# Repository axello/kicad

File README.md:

# kicad playground

Just starting with kicad, this is a hodgepodge of small electronics projects, mostly centered around the ESP8266.

## ESP-RS232
A small-footprint design to connect an ESP8266 to a DB9 RS232 interface. Useful to connect to powerbars, power supplies, air quality sensors, solar panel controllers and whatnot.

## ESP-Sensors
A design to test the non-breadboardable ESP8266-12E with various sensors. It has a small prototyping area to solder different sensors on.

## GettingToBlinky
First kicad tutorial by [Contextual Electronics](https://www.youtube.com/watch?v=JN_Y93RTdSo&list=PLy2022BX6Eso532xqrUxDT1u2p4VVsg-q>)

## NodeMCU-Metriful
I wanted to hook up the Kickstarted [Metriful](https://www.kickstarter.com/projects/metriful/sense-indoor-environment-monitor/) project to my mqtt system, so needed to hook it up to the wifi. I decided to use the plethora of NodeMCUs I had laying around and made this dedicated circuit board for it. As a bonus it allows adding a chain of DS18B20 temperature sensors.
I also designed a 3D printable case for it, which you can find [here](https://cad.onshape.com/documents/7fa239791ccb4fa3d67e6539/w/d93b090168ac9bb29c0ad025/e/45795b691b4838ca7b8d4e6e).

## libs
My components

## mods
My footprints

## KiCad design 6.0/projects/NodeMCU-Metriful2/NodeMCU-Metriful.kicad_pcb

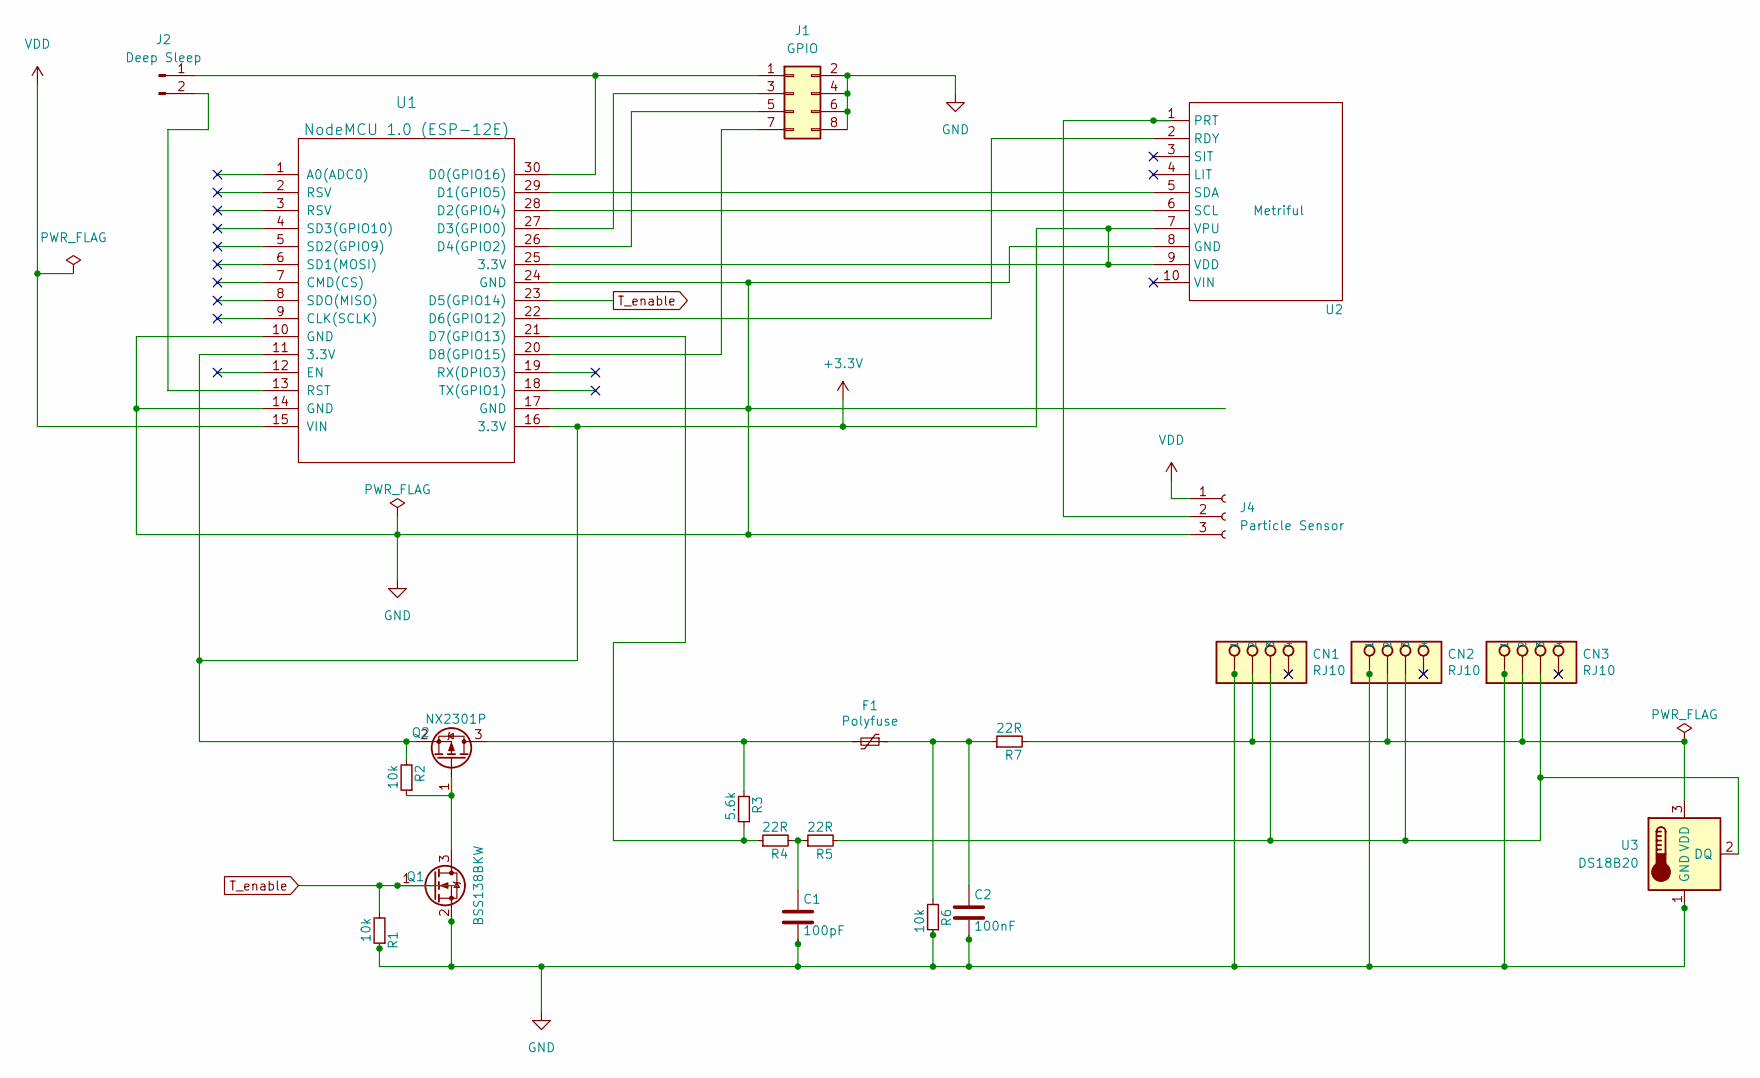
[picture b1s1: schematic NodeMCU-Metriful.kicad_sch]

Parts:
C1: 100pF; C_0805_2012Metric_Pad1.18x1.45mm_HandSolder
C2: 100nF; C_0805_2012Metric
CN1, CN2, CN3: RJ10; rj10
F1: Polyfuse; Fuse_1210_3225Metric_Pad1.42x2.65mm_HandSolder
J1: GPIO; PinHeader_2x04_P2.54mm_Vertical
J2: Deep Sleep; PinHeader_1x02_P2.54mm_Vertical
J4: Particle Sensor; JST_PH_B3B-PH-K_1x03_P2.00mm_Vertical
Q1: BSS138BKW; SOT-323_SC-70_Handsoldering
Q2: NX2301P; SOT-23-3
R1, R2, R6: 10k; R_0805_2012Metric_Pad1.20x1.40mm_HandSolder
R3: 5.6k; R_0805_2012Metric_Pad1.20x1.40mm_HandSolder
R4, R5, R7: 22R; R_0805_2012Metric_Pad1.20x1.40mm_HandSolder
U1: NodeMCU 1.0 (ESP-12E); NodeMCU_0.1_Axel
U2: Metriful; Metriful-1
U3: DS18B20; TO-92_Inline

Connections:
+3V3: Q2.2 (S), R2.2, U1.11 (3.3V), U1.16 (3.3V), U1.25 (3.3V), U2.7 (VPU), U2.9 (VDD)
GND: C1.2, C2.2, CN1.1, CN2.1, CN3.1, J1.2, J1.4, J1.6, J1.8, J4.3, Q1.2 (S), R1.1, R6.1, U1.10 (GND), U1.14 (GND), U1.17 (GND), U1.24 (GND), U2.8 (GND), U3.1 (GND)
unnamed: C1.1, R4.2, R5.1
unnamed: C2.1, F1.1, R6.2, R7.1
unnamed: CN1.2, CN2.2, CN3.2, R7.2, U3.3 (VDD)
unnamed: CN1.3, CN2.3, CN3.3, R5.2, U3.2 (DQ)
unnamed: F1.2, Q2.3 (D), R3.2
unnamed: J1.1 (D0), J2.1, U1.30 (D0(GPIO16))
unnamed: J1.3 (D3), U1.27 (D3(GPIO0))
unnamed: J1.5 (D4), U1.26 (D4(GPIO2))
unnamed: J1.7 (D8), U1.20 (D8(GPIO15))
unnamed: J2.2, U1.13 (RST)
unnamed: J4.2, U2.1 (PRT)
unnamed: Q1.3 (D), Q2.1 (G), R2.1
unnamed: R3.1, R4.1, U1.21 (D7(GPIO13))
unnamed: U1.22 (D6(GPIO12)), U2.2 (RDY)
unnamed: U1.28 (D2(GPIO4)), U2.6 (SCL)
unnamed: U1.29 (D1(GPIO5)), U2.5 (SDA)
T_enable: Q1.1 (G), R1.2, U1.23 (D5(GPIO14))
VDD: J4.1, U1.15 (VIN)

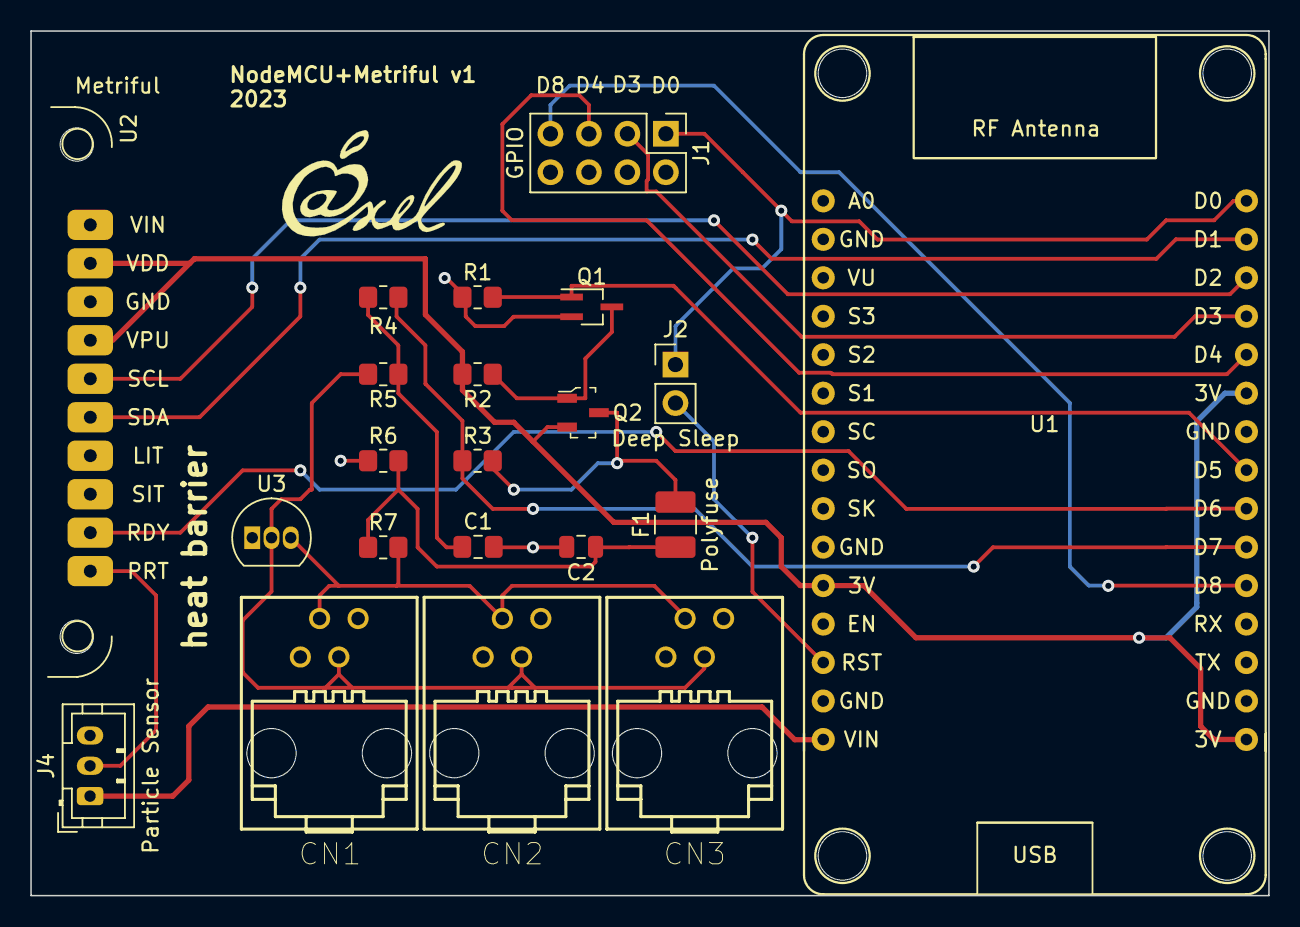
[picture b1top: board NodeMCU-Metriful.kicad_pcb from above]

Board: 2 copper layers, 81.7 x 57.1 mm, 21 parts (0 on the bottom side), 20 nets.

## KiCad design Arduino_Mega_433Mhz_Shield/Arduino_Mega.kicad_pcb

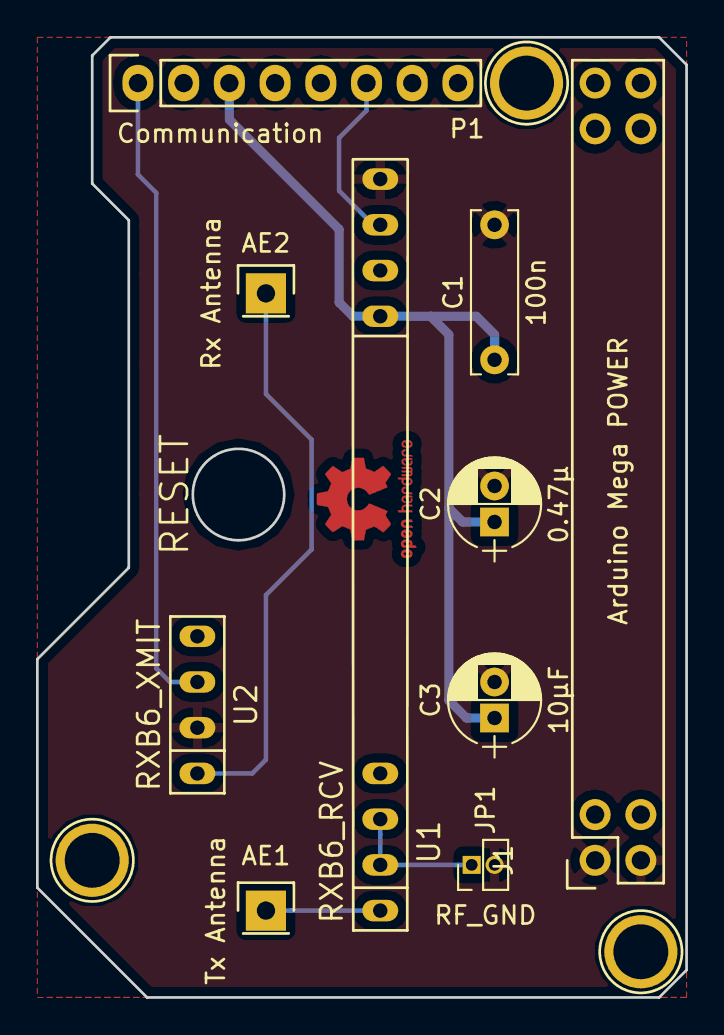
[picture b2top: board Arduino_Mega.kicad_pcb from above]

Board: 2 copper layers, 36.1 x 53.3 mm, 13 parts (0 on the bottom side), 8 nets.

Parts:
AE1: Tx Antenna; Pin_Header_Straight_1x01
AE2: Rx Antenna; Pin_Header_Straight_1x01
C1: 100n; C_Rect_L9.0mm_W2.5mm_P7.50mm_MKT
C2: 0.47µ; CP_Radial_D5.0mm_P2.00mm
C3: 10µF; CP_Radial_D5.0mm_P2.00mm
J1: Arduino Mega POWER; Power_Strip_Arduino_Mega_2x18
JP1: RF_GND; Pin_Header_Straight_1x02_Pitch1.27mm
P1: Communication; Socket_Strip_Arduino_1x08
P9, P10, P13: CONN_01X01; Arduino_1pin
U1: RXB6_RCV; RCV
U2: RXB6_XMIT; XMIT

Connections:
+5V: J1.35, J1.36, U2.4
/14(Tx3): P1.1, U2.3
/16(Tx2): C1.1, C2.1, C3.1, P1.3, U1.5
/19(Rx1): P1.6, U1.7
GND: C1.2, C2.2, C3.2, J1.1, J1.2, JP1.2, U1.8, U2.2
unnamed: AE1.1, U1.1
unnamed: AE2.1, U2.1
unnamed: JP1.1, U1.2, U1.3

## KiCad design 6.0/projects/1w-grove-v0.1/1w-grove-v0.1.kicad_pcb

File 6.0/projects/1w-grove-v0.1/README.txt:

# 1w-esp32

2021-01-30  v0.2 - version based on the rs485-esp32-v0.3 version and updated to a sub schematic
                 - Had to replace all components after moving them to the sun schema

# end

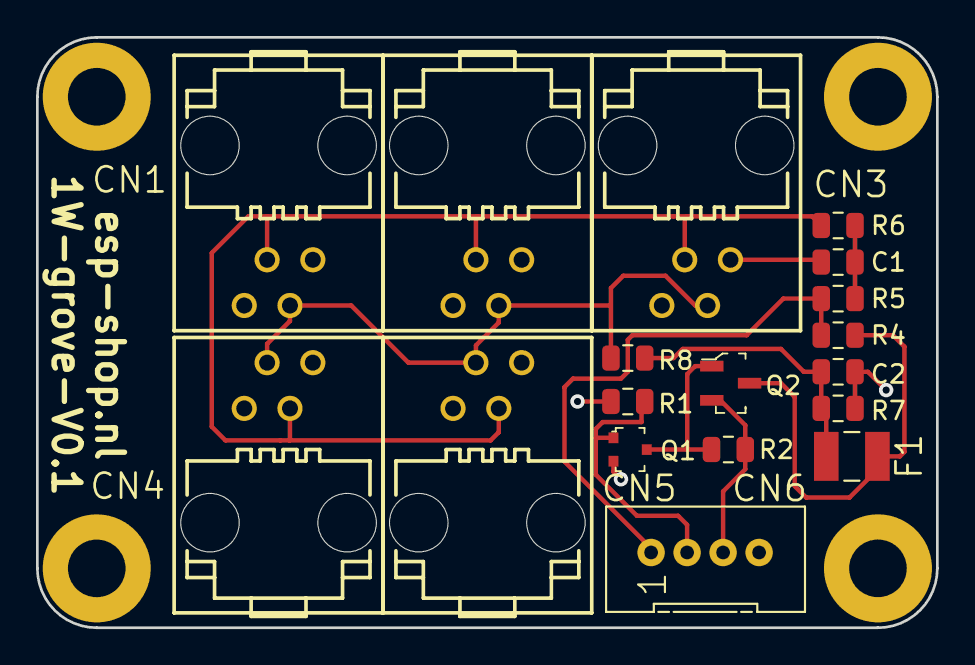
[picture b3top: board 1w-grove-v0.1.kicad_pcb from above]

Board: 2 copper layers, 50.0 x 32.8 mm, 23 parts (1 on the bottom side), 10 nets.

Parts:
C1: 100pF; C_0805_2012Metric
C2: 100nF; C_0805_2012Metric
CN1, CN2, CN3, CN4, CN5: RJ10; rj10-v2
CN6: grove; grove-v0.1
F1: Polyfuse_Small; C1210
Q1: BSS138BKW; SOT-323
Q2: NX2301P; SOT-23-3
R1, R2, R7: 10k; R_0805_2012Metric
R4: 5.6k; R_0805_2012Metric
R5, R6, R8: 22R; R_0805_2012Metric
U3: CE-mark; CE-140
U4, U6, U10, U11: schroef_3.5mm

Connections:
unnamed: C1.1, R5.2, R6.1
unnamed: C1.2, C2.2, CN1.1, CN2.1, CN3.1, CN4.1, CN5.1, CN6.4, Q1.2 (S), R1.1, R7.1
unnamed: C2.1, F1.1, R7.2, R8.1
unnamed: CN1.2, CN2.2, CN3.2, CN4.2, CN5.2, R8.2
unnamed: CN1.3, CN2.3, CN3.3, CN4.3, CN5.3, R6.2
unnamed: F1.2, Q2.3 (D), R4.2
unnamed: CN6.2, Q1.1 (G), R1.2
unnamed: Q1.3 (D), Q2.1 (G), R2.1
unnamed: CN6.3, Q2.2 (S), R2.2
unnamed: CN6.1, R4.1, R5.1

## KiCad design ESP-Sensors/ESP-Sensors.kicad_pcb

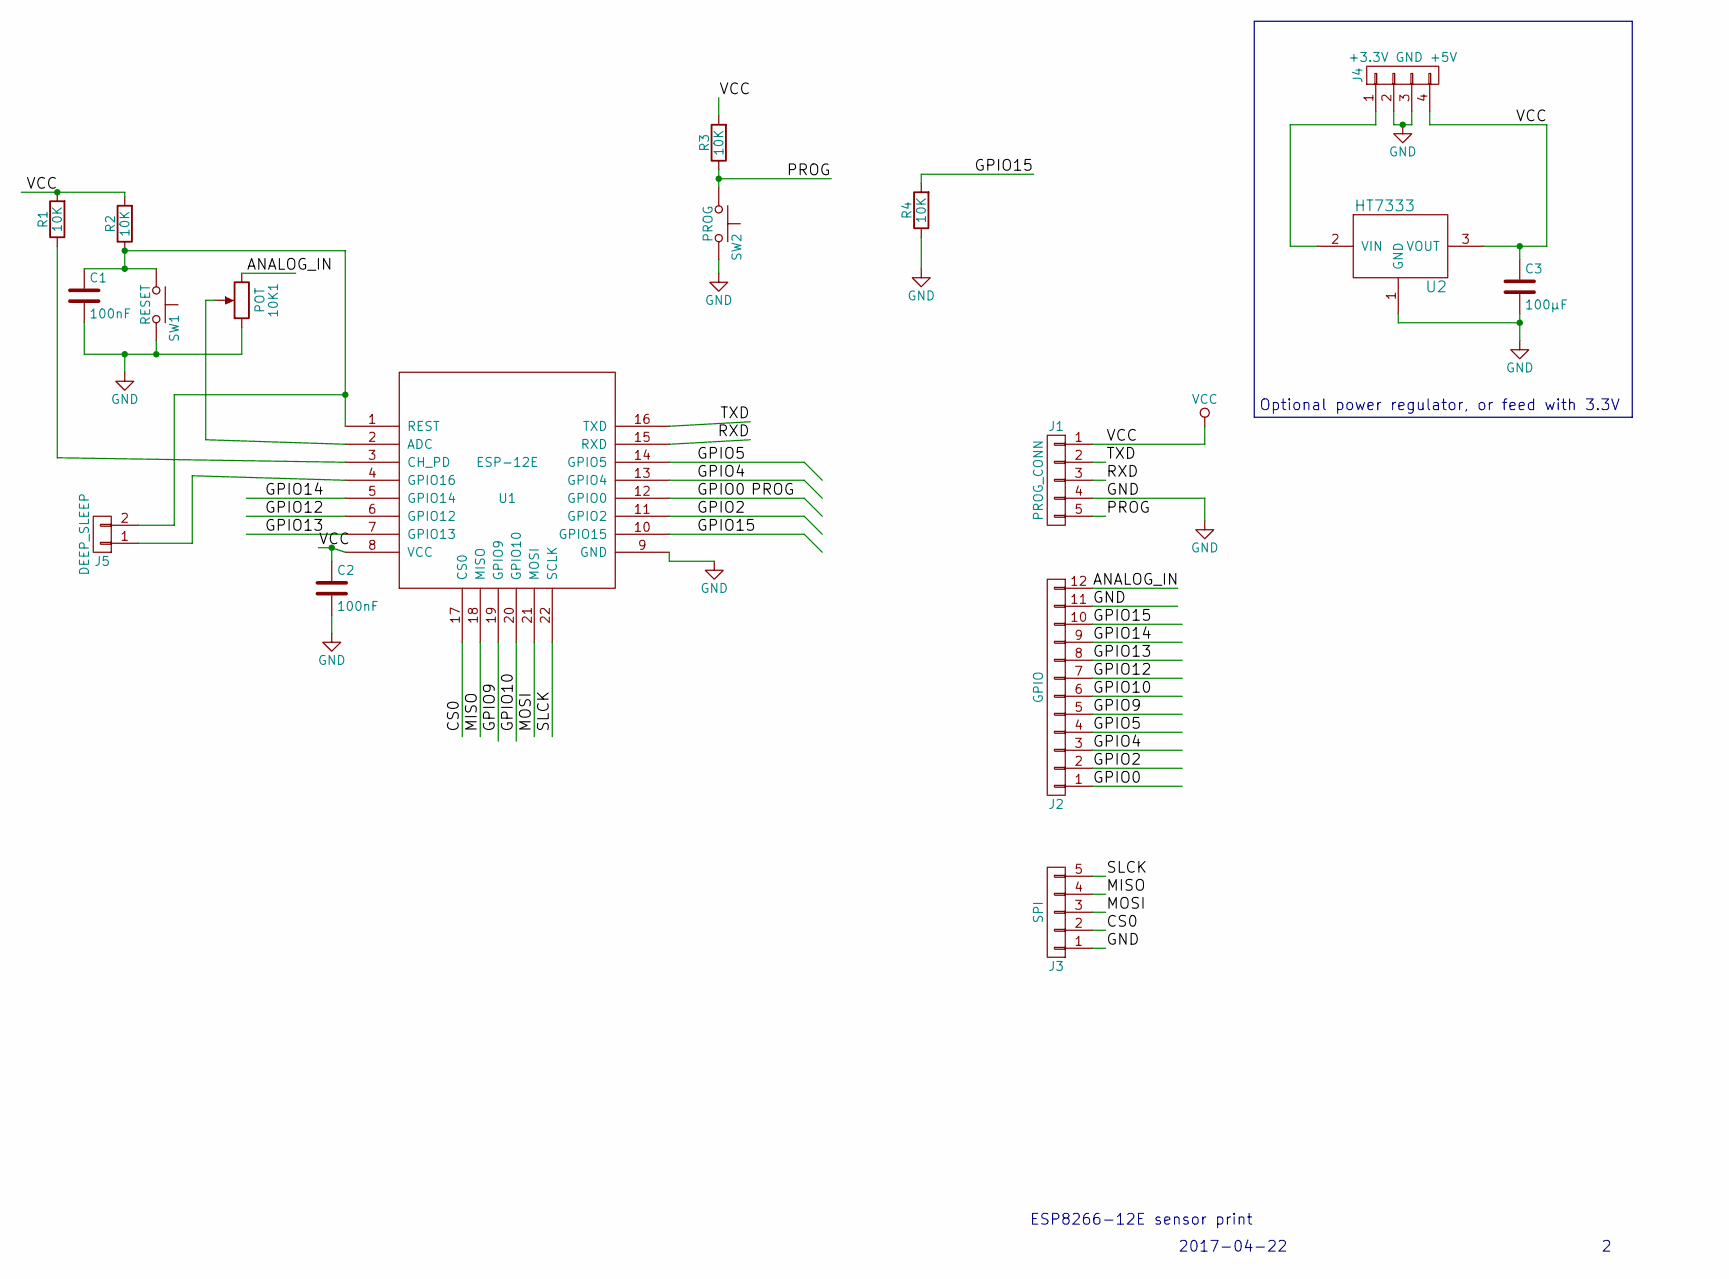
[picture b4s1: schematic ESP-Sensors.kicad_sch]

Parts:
10K1: POT; Potentiometer_Trimmer_Vishay_T73YP_Horizontal
C1, C2: 100nF; C_0805_HandSoldering
C3: 100µF; c_elec_6.3x7.7
J1: PROG_CONN; Pin_Header_Straight_1x05b
J2: GPIO; Pin_Header_Straight_1x12
J3: SPI; SPI_Header
J4: +3.3V GND +5V; Pin_Header_Straight_1x04
J5: DEEP_SLEEP; Pin_Header_Straight_1x02
R1, R2, R3, R4: 10K; R_0805_HandSoldering
SW1: RESET; SW_PUSH_6mm
SW2: PROG; SW_PUSH_6mm
U1: ESP-12E
U2: HT7333; SOT89-3_Housing_Handsoldering

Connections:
/ANALOG_IN: 10K1.3, J2.12
/CS0: J3.2, U1.17 (CS0)
/GPIO0: J1.5, J2.1, R3.1, SW2.1, U1.12 (GPIO0)
/GPIO2: J2.2, U1.11 (GPIO2)
/GPIO4: J2.3, U1.13 (GPIO4)
/GPIO5: J2.4, U1.14 (GPIO5)
/GPIO9: J2.5, U1.19 (GPIO9)
/GPIO10: J2.6, U1.20 (GPIO10)
/GPIO12: J2.7, U1.6 (GPIO12)
/GPIO13: J2.8, U1.7 (GPIO13)
/GPIO14: J2.9, U1.5 (GPIO14)
/GPIO15: J2.10, R4.2, U1.10 (GPIO15)
/MISO: J3.4, U1.18 (MISO)
/MOSI: J3.3, U1.21 (MOSI)
/RXD: J1.3, U1.15 (RXD)
/SLCK: J3.5, U1.22 (SCLK)
/TXD: J1.2, U1.16 (TXD)
GND: 10K1.1, C1.2, C2.2, C3.2, J1.4, J2.11, J3.1, J4.2, J4.3, R4.1, SW1.2, SW2.2, U1.9 (GND), U2.1 (GND)
unnamed: 10K1.2, U1.2 (ADC)
unnamed: C1.1, J5.2, R2.1, SW1.1, U1.1 (REST)
unnamed: J4.1, U2.2 (VIN)
unnamed: J5.1, U1.4 (GPIO16)
unnamed: R1.1, U1.3 (CH_PD)
VCC: C2.1, C3.1, J1.1, J4.4, R1.2, R2.2, R3.2, U1.8 (VCC), U2.3 (VOUT)

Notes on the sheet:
2017-04-22
ESP8266-12E sensor print
Optional power regulator, or feed with 3.3V

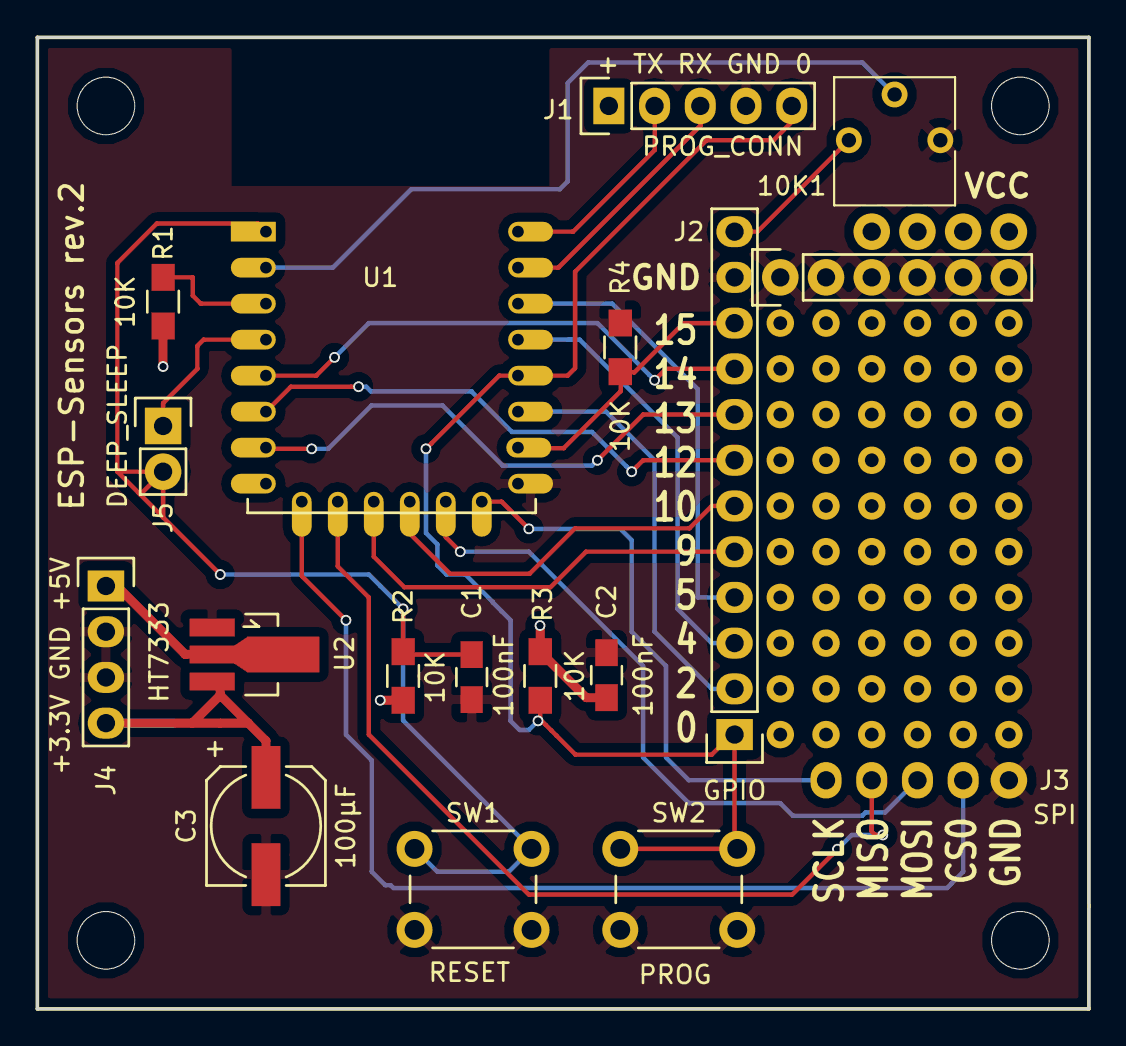
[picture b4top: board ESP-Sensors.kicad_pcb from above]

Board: 2 copper layers, 58.4 x 54.0 mm, 17 parts (0 on the bottom side), 24 nets.

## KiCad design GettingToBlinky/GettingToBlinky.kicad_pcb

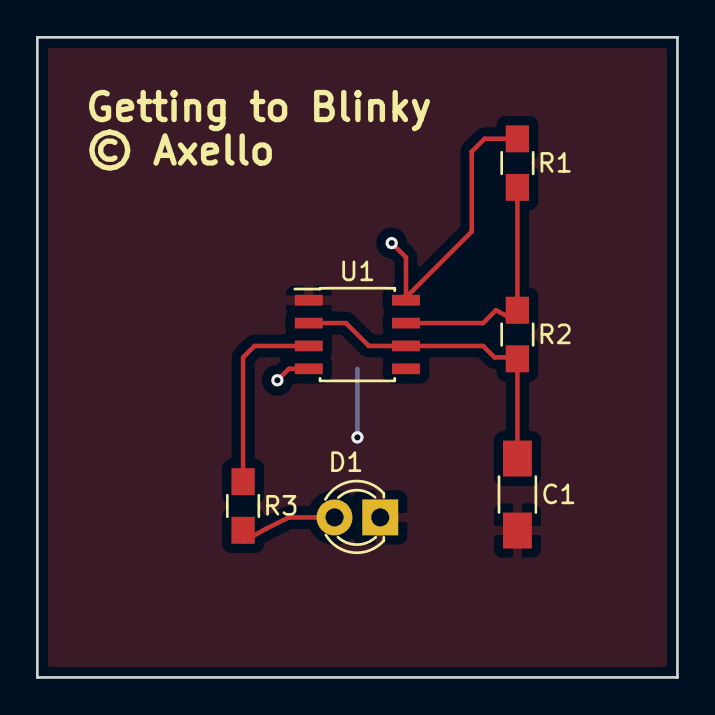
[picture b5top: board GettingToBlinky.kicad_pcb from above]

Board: 2 copper layers, 35.6 x 35.6 mm, 7 parts (1 on the bottom side), 6 nets.

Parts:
BT1: Battery; BatteryHolder
C1: 1µF; C_1206_HandSoldering
D1: LED; LED-3MM
R1, R3: 1K; R_0805_HandSoldering
R2: 470K; R_0805_HandSoldering
U1: 7555; SOIC-8_3.9x4.9mm_Pitch1.27mm

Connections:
/VDD: BT1.1, R1.1, U1.4, U1.8
GND: BT1.2, C1.2, D1.1, U1.1
unnamed: C1.1, R2.2, U1.2, U1.6
unnamed: D1.2, R3.2
unnamed: R1.2, R2.1, U1.7
unnamed: R3.1, U1.3

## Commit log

2017-03-28 first post
2017-03-28 created Blinky schematic
2017-03-28 created net list
2017-03-28 created correct net list
2017-03-28 finished pcb layout
2017-03-28 Created gerber files
2017-03-28 removed pin5 connection, re-generated pcb
2017-03-30 First draft of ESP-RS232 tool
2017-03-30 fixed ERC with power outlets
2017-04-02 started with pcb tracing of esp-sensor
2017-04-03 Cleanup libraries and modules to central place
2017-04-03 Added readme
2017-04-03 fixed U2 power connection, more traces
2017-04-03 all traced layed out, DRC, labels correct
2017-04-03 re-routed ground + analog
2017-04-03 Created gerbers, checkup
2017-04-03 More cleanup of vias
2017-04-03 added different trimmer plus deep_sleep jumper header
2017-04-03 First iteration RS232 ESP8266 schematic
2017-04-05 Added GPIO refs again and added VCC header
2017-04-05 staged for OSHPark rev.1
2017-05-06 Fixed ESP-Sensors board (ht7333 wrong footprint):rev 2
2017-05-10 created and added images of schematics and pcb
2022-11-15 add kicad 6 projects and added libraries
2022-11-15 added dsstore to gitignore
2023-05-21 Add NodeMCU-Metriful project
2023-05-21 Add 1wire+grove project + libraries from Martin
2023-05-21 Add backups for ESP-Sensors print
2023-05-22 Made print smaller, moved RJ10 upwards, as they're straight Also discovered that my NodeMCUs are WIDER. So this is before that change.
2023-05-23 Final (?) version, eliminated the severe warnings.
2023-05-23 Add header, move components to the left to make room for deep-sleep pin header
2023-05-23 Many last-minute changes, mostly to silkscreen and some positioning
2023-06-07 old zip files
2023-06-13 remove doubly-linked connections
2023-10-20 update readme with NodeMCU-Metriful project

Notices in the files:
GettingToBlinky/GettingToBlinky.kicad_pcb:
© Axello
